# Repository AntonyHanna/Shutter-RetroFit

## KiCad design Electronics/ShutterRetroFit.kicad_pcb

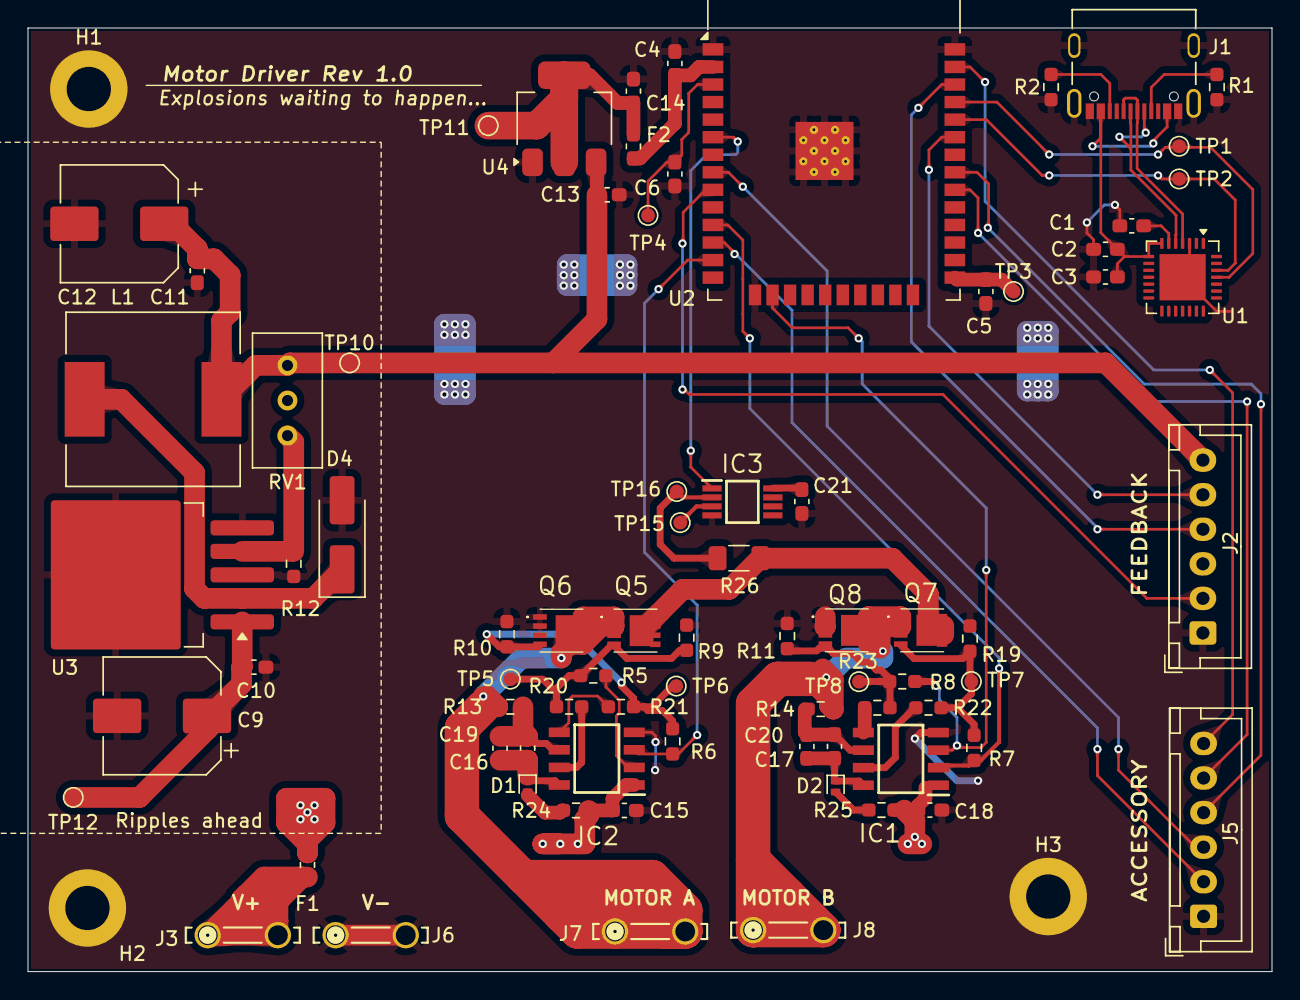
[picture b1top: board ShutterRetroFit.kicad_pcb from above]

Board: 2 copper layers, 90.0 x 68.3 mm, 80 parts (0 on the bottom side), 52 nets.

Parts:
C1, C3, C5, C6, C14, C15, C16, C17, C18, C21: 0.1uF; C_0603_1608Metric_Pad1.08x0.95mm_HandSolder
C2, C13: 1uF; C_0603_1608Metric_Pad1.08x0.95mm_HandSolder
C4, C19, C20: 22uF; C_0603_1608Metric_Pad1.08x0.95mm_HandSolder
C9: 100; CP_Elec_8x10
C10, C11: 100; C_0603_1608Metric_Pad1.08x0.95mm_HandSolder
C12: 220; CP_Elec_8x10
D1, D2: RB751ASA-40FHT2RB; D_SOD-882_Handsoldered
D4: SS34; D_SMA_Handsoldering
F1: MOTOR; Fuse_0603_1608Metric_Pad1.05x0.95mm_HandSolder
F2: CONTROL (1A); Fuse_0603_1608Metric_Pad1.05x0.95mm_HandSolder
H1, H2, H3: MountingHole_Pad; MountingHole_3.2mm_M3_DIN965_Pad
IC1, IC2: NCP5104DR2G; SOIC127P600X175-8N
IC3: INA2180A2QDGKRQ1; SOP65P490X110-8N
J1: AMPHENOL_12402012E212A
J2: ACCESSORY; JST_XH_B6B-XH-A_1x06_P2.50mm_Vertical
J3: PWR_IN+; CONN_726386-2_TEC
J5: CONTROL; JST_XH_B6B-XH-A_1x06_P2.50mm_Vertical
J6: PWR_IN-; CONN_726386-2_TEC
J7: Motor A; CONN_726386-2_TEC
J8: Motor B; CONN_726386-2_TEC
L1: 47uH; L_12x12mm_H8mm
Q5, Q6, Q7, Q8: SiSS52DN-T1-GE3; SISS94DNT1GE3
R1, R2: 5k1; R_0603_1608Metric_Pad0.98x0.95mm_HandSolder
R5, R6, R7, R8, R13, R14: 0; R_0603_1608Metric_Pad0.98x0.95mm_HandSolder
R9, R10, R11, R19: 5k; R_0603_1608Metric_Pad0.98x0.95mm_HandSolder
R12: 265; R_0603_1608Metric_Pad0.98x0.95mm_HandSolder
R20, R21, R22, R23, R24, R25: 1k; R_0603_1608Metric_Pad0.98x0.95mm_HandSolder
R26: MFSA1206R0100FCM; R_1206_3216Metric_Pad1.30x1.75mm_HandSolder
RV1: R_Potentiometer_Trim; Potentiometer_Bourns_3296W_Vertical
TP1: RX; TestPoint_Pad_D1.0mm
TP2: TX; TestPoint_Pad_D1.0mm
TP3, TP5, TP6, TP7, TP8: IO0; TestPoint_Pad_D1.0mm
TP4: EN; TestPoint_Pad_D1.0mm
TP10: 5V; TestPoint_Pad_D1.0mm
TP11: 3V; TestPoint_Pad_D1.0mm
TP12: +12V; TestPoint_Pad_D1.0mm
TP15: V-; TestPoint_Pad_D1.0mm
TP16: V+; TestPoint_Pad_D1.0mm
U1: CP2102-Axx-xQFN28; QFN-28-1EP_5x5mm_P0.5mm_EP3.35x3.35mm
U2: ESP32-WROOM-32
U3: LM2596S-ADJ; TO-263-5_TabPin3
U4: AMS1117-3.3 (Potentially swap for a better LDO); SOT-223-3_TabPin2

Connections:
+5V_{LREG}: C11.1, C12.1, C13.1, J2.6, L1.2, RV1.3, TP10.1, U4.3 (VI)
+5v_{EXP}: C21.1, IC3.8 (VS)
+12V: F1.1, J3.1, J3.2
+12V_{MOTOR}: C9.1, C10.1, TP12.1, U3.1 (VIN)
+12v_{EXP}: C15.1, C18.1, F1.2, IC1.1 (VCC), IC2.1 (VCC), R24.1, R25.1
/+3v3: C4.1, F2.2, U2.2 (VDD)
/BTN_{DOWN}: J5.3, U2.8 (IO32)
/BTN_{UP}: J5.2, U2.12 (IO27)
/DATA+: J1.A6 (D+_A), J1.B6 (D+_B), U1.4 (D+)
/DATA-: J1.A7 (D-_A), J1.B7 (D-_B), U1.5 (D-)
/D_{ERROR}: J5.4, U2.31 (IO19)
/D_{POWER}: J5.6, U2.37 (IO23)
/D_{STATUS}: J5.5, U2.30 (IO18)
/EN: C6.1, TP4.1, U2.3 (EN)
/H_{DRIVER_LEFT_CONTROL}: IC2.2 (IN), R5.2
/H_{DRIVER_LEFT_EN}: IC2.3 (~SD), R6.2, U2.13 (IO14)
/H_{DRIVER_RIGHT_CONTROL}: IC1.2 (IN), R7.2, U2.11 (IO26)
/H_{DRIVER_RIGHT_EN}: IC1.3 (~SD), R8.2, U2.16 (IO13)
/IO0: C5.1, TP3.1, U2.25 (IO0)
/IO33: J2.2, U2.9 (IO33)
/M_{SENSE}: IC3.1 (OUT1), U2.6 (IO34)
/Motor/L_{HI}: Q5.4 (G), R5.1, R9.2, R20.2, TP5.1
/Motor/L_{LO}: Q6.4 (G), R6.1, R10.2, R21.1, TP6.1
/Motor/L_{MID}: J7.1, J7.2, Q5.1 (S_1), Q5.2 (S_2), Q5.3 (S_3), Q6.5 (D_1), Q6.6 (D_2), Q6.7 (D_3), Q6.8 (D_4), Q6.9 (D_5), Q6.10 (D_6), Q6.11 (D_7), R13.2
/Motor/M_{SUPPLY}: Q5.5 (D_1), Q5.6 (D_2), Q5.7 (D_3), Q5.8 (D_4), Q5.9 (D_5), Q5.10 (D_6), Q5.11 (D_7), Q7.5 (D_1), Q7.6 (D_2), Q7.7 (D_3), Q7.8 (D_4), Q7.9 (D_5), Q7.10 (D_6), Q7.11 (D_7), R26.2
/Motor/R_{HI}: Q7.4 (G), R7.1, R19.2, R22.2, TP7.1
/Motor/R_{LO}: Q8.4 (G), R8.1, R11.2, R23.1, TP8.1
/Motor/R_{MID}: J8.1, J8.2, Q7.1 (S_1), Q7.2 (S_2), Q7.3 (S_3), Q8.5 (D_1), Q8.6 (D_2), Q8.7 (D_3), Q8.8 (D_4), Q8.9 (D_5), Q8.10 (D_6), Q8.11 (D_7), R14.2
/SENS_{SCL}: J2.4, U2.36 (IO22)
/SENS_{SDA}: J2.5, U2.33 (IO21)
/UART_{RX}: TP1.1, U1.25 (RXD), U2.35 (TXD0/IO1)
/UART_{TX}: TP2.1, U1.26 (TXD), U2.34 (RXD0/IO3)
/USB_{VBUS}: C2.1, C3.1, J1.A4_B9 (VBUS), J1.B4_A9 (VBUS__1), U1.7 (VREGIN), U1.8 (VBUS)
GND: C1.2, C2.2, C3.2, C4.2, C5.2, C6.2, C9.2, C10.2, C11.2, C12.2, C13.2, C14.2, C15.2, C18.2, C21.2, D4.2 (A), H1.1, H2.1, H3.1, IC1.4 (GND), IC2.4 (GND), IC3.4 (GND), J1.A1_B12 (GND), J1.B1_A12 (GND__1), J1.SH1 (SHIELD), J1.SH2 (SHIELD__1), J1.SH3 (SHIELD__2), J1.SH4 (SHIELD__3), J2.1, J5.1, J6.1, J6.2, Q6.1 (S_1), Q6.2 (S_2), Q6.3 (S_3), Q8.1 (S_1), Q8.2 (S_2), Q8.3 (S_3), R1.2, R2.2, R9.1, R10.1, R11.1, R12.2, R19.1, U1.3 (GND), U1.29 (GND), U2.1 (GND), U2.15 (GND), U2.38 (GND), U2.39 (GND), U3.3 (GND), U3.5 (~ON/OFF), U4.1 (GND)
unnamed: D1.2 (A), R24.2
unnamed: C16.2, C19.2, D1.1 (K), IC2.8 (VBOOT)
unnamed: D2.2 (A), R25.2
unnamed: C17.2, C20.2, D2.1 (K), IC1.8 (VBOOT)
unnamed: D4.1 (K), L1.1, U3.2 (OUT)
unnamed: C17.1, C20.1, IC1.6 (BRIDGE), R14.1
unnamed: IC1.7 (DRV_HI), R22.1
unnamed: IC1.5 (DRV_LO), R23.2
unnamed: C16.1, C19.1, IC2.6 (BRIDGE), R13.1
unnamed: IC2.7 (DRV_HI), R20.1
unnamed: IC2.5 (DRV_LO), R21.2
unnamed: IC3.3 (IN+1), TP15.1
unnamed: IC3.2 (IN-1), R26.1, TP16.1
unnamed: J1.A5 (CC1_A), R1.1
unnamed: J1.B5 (CC1_B), R2.1
unnamed: C1.1, U1.6 (VDD)
unnamed: R12.1, RV1.1, U3.4 (FB)
unnamed: C14.1, F2.1, TP11.1, U4.2 (VO)

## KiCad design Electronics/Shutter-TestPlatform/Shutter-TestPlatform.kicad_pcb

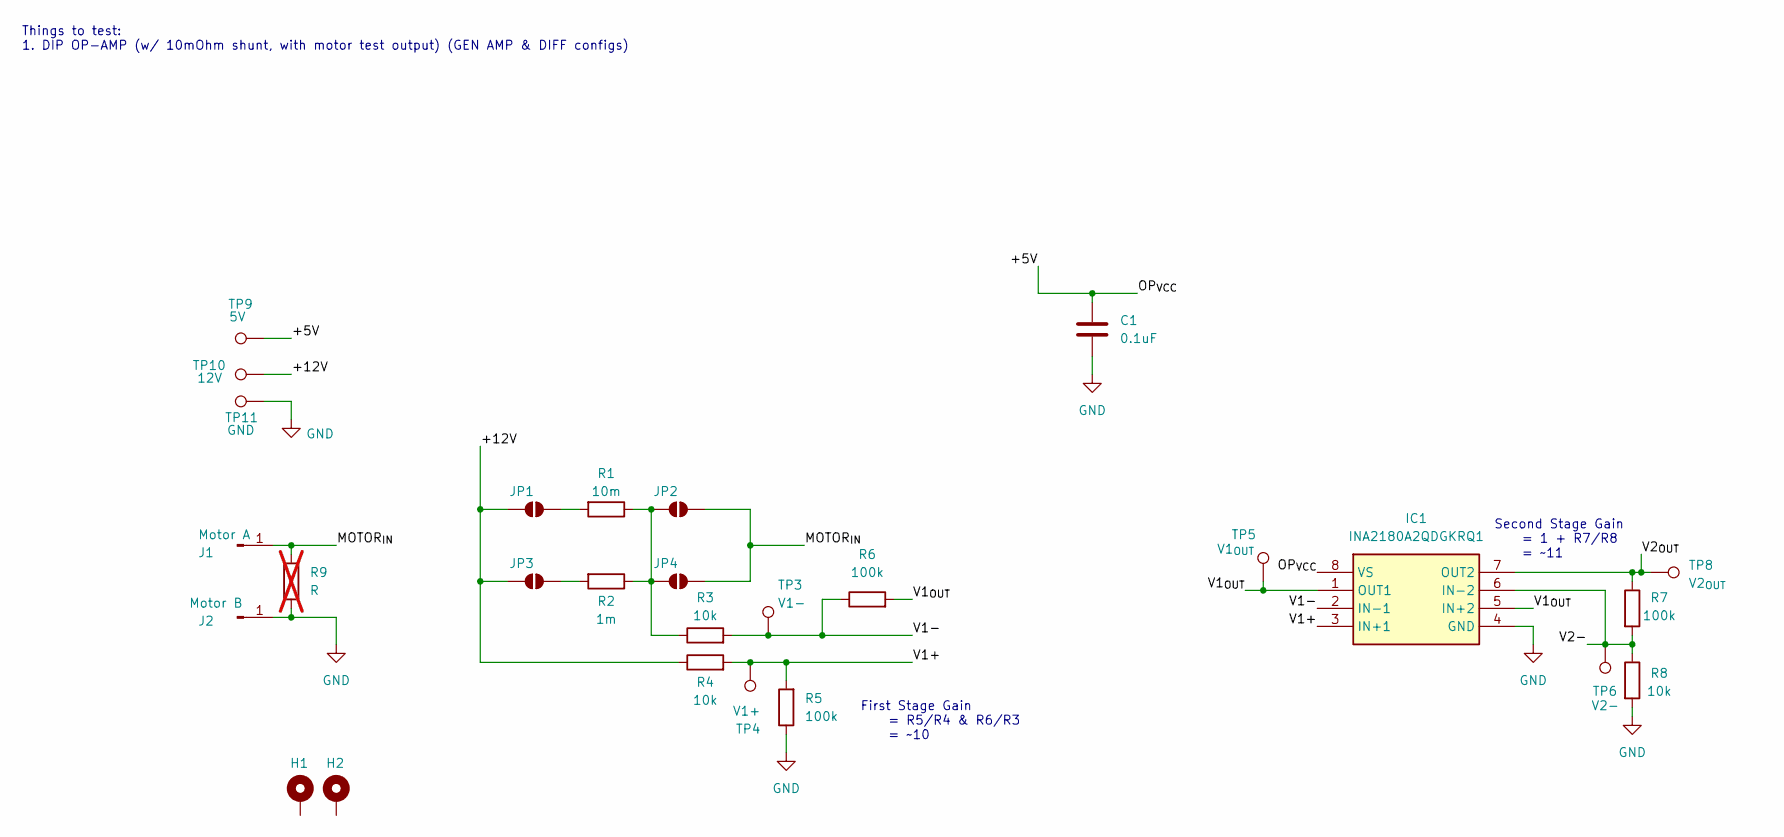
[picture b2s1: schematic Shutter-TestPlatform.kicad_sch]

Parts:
C1: 0.1uF; C_0603_1608Metric_Pad1.08x0.95mm_HandSolder
H1, H2: MountingHole_Pad; MountingHole_3.2mm_M3_DIN965_Pad
IC1: INA2180A2QDGKRQ1; SOP65P490X110-8N; Mouser Part Number 595-INA2180A2QDGKRQ1
J1: Motor A; CONN_726386-2_TEC
J2: Motor B; CONN_726386-2_TEC
JP1, JP2, JP3, JP4: SolderJumper_2_Open; SolderJumper-2_P1.3mm_Open_RoundedPad1.0x1.5mm
R1: 10m; R_1206_3216Metric_Pad1.30x1.75mm_HandSolder
R2: 1m; R_2512_6332Metric_Pad1.40x3.35mm_HandSolder
R3, R4, R8: 10k; R_0603_1608Metric_Pad0.98x0.95mm_HandSolder
R5, R6, R7: 100k; R_0603_1608Metric_Pad0.98x0.95mm_HandSolder
R9: R; R_Axial_DIN0207_L6.3mm_D2.5mm_P10.16mm_Horizontal; not fitted
TP3: V1-; TestPoint_Pad_D3.0mm
TP4: V1+; TestPoint_Pad_D3.0mm
TP5: V1_{OUT}; TestPoint_Pad_D3.0mm
TP6: V2-; TestPoint_Pad_D3.0mm
TP8: V2_{OUT}; TestPoint_Pad_D3.0mm
TP9: 5V; TestPoint_Pad_D3.0mm
TP10: 12V; TestPoint_Pad_D3.0mm
TP11: GND; TestPoint_Pad_D3.0mm

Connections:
/+5V: C1.1, IC1.8 (VS), TP9.1
/+12V: JP1.2 (B), JP3.2 (B), R4.1, TP10.1
/MOTOR_{IN}: J1.1, JP2.1 (A), JP4.1 (A), R9.1
/V1+: IC1.3 (IN+1), R4.2, R5.2, TP4.1
/V1-: IC1.2 (IN-1), R3.2, R6.1, TP3.1
/V1_{OUT}: IC1.1 (OUT1), IC1.5 (IN+2), R6.2, TP5.1
/V2-: IC1.6 (IN-2), R7.2, R8.1, TP6.1
/V2_{OUT}: IC1.7 (OUT2), R7.1, TP8.1
GND: C1.2, IC1.4 (GND), J2.1, R5.1, R8.2, R9.2, TP11.1
unnamed: JP1.1 (A), R1.2
unnamed: JP2.2 (B), JP4.2 (B), R1.1, R2.1, R3.1
unnamed: JP3.1 (A), R2.2

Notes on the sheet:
Second Stage Gain = 1 + R7/R8 = ~11
First Stage Gain = R5/R4 & R6/R3 = ~10
Things to test: 1. DIP OP-AMP (w/ 10mOhm shunt, with motor test output) (GEN AMP & DIFF configs)

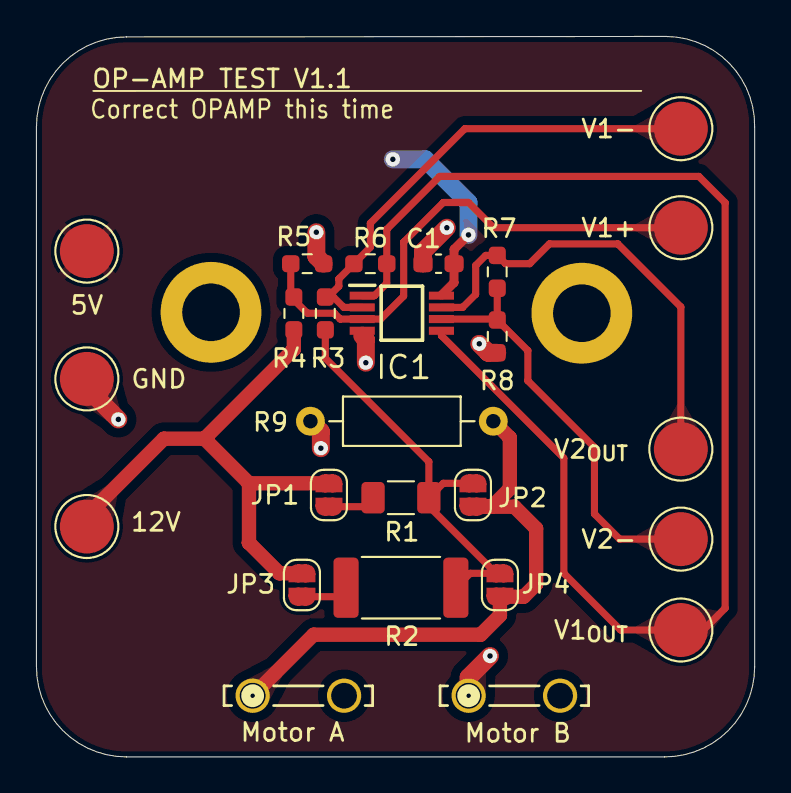
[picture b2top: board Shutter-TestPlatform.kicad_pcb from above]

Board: 2 copper layers, 39.9 x 40.0 mm, 27 parts (0 on the bottom side), 12 nets.

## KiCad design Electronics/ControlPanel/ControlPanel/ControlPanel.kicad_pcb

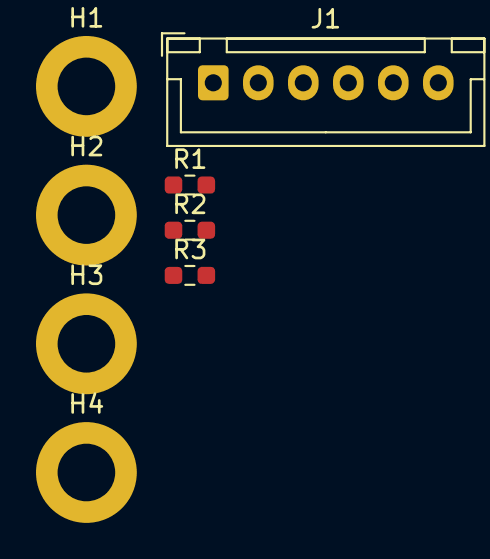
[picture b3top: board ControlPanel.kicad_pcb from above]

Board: 2 copper layers, 8 parts (0 on the bottom side), 4 nets, no tracks yet.

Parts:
H1, H2, H3, H4: MountingHole_Pad; MountingHole_3.2mm_M3_DIN965_Pad
J1: CONTROL; JST_XH_B6B-XH-A_1x06_P2.50mm_Vertical
R1, R2, R3: 100; R_0603_1608Metric_Pad0.98x0.95mm_HandSolder

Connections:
/D_{ERROR}: J1.4, R3.2
/D_{POWER}: J1.6, R1.2
/D_{STATUS}: J1.5, R2.2
GND: H1.1, H2.1, H3.1, H4.1, J1.1

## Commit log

2025-10-05 Bulk sync with various changes made over the last year
2025-10-05 Update control panel files to newer Kicad version
2025-10-05 Clean up schematic to be neater and repurposed AS5600 to be generic accessory connector
2026-01-18 Electronics release 1.0
2026-01-23 Add some possible functions that will properly be implemented later
2026-02-15 Add basic code for generating PWM, light sequences and controlling the dual half bridge drivers
2026-02-15 Fix failing build of basic logic
2026-02-15 Motor drive and reverse working
2026-02-16 Remove unnessecary error assignment
2026-02-16 Move AS5600 sensor logic to a seperate class
